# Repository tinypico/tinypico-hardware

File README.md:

# tinypico-hardware
Hardware design files for TinyPICO and Shields

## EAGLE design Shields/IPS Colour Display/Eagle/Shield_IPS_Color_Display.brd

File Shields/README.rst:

TinyPICO Hardware
=================

In this repository, you'll find Eagle 9.x design files and gerbers for the TinyPICO shields we design ourselves.

Gerber files are provided in 274X format.

As we release new shields and designed, we will add them here. 

Open Source License
-------------------

These files are released as open source under the CERN license. Please review the license before using these files in your own projects to understand your obligations.

TinyPICO Branding
-----------------
The name TinyPICO, logos and TinyPICO brand are owned by Unexpected Maker. If you would like to use the name in a project you are making that supports the TinyPICO hardware, please contact us and we'll be happy to talk to you about it.

Support Unexpected Maker
------------------------

We love designing, making and releasing our projects as open source. We do it because we believe it’s important to share knowledge and give back to the community as many have done before us. It helps us all learn and grow.

That said, a lot of time, effort and finances have gone into designing and releasing these files, so please consider supporting us by backing TinyPICO on our Crowd Supply campaign:

https://www.crowdsupply.com/unexpected-maker/tinypico

Or by buying one of our products on tindie or our own shop:

https://www.tindie.com/stores/seonr/
https://unexpectedmaker.com/shop

Or by becoming a Patron:

https://www.patreon.com/unexpectedmaker

Unexpected Maker
===================
http://youtube.com/c/unexpectedmaker

http://twitter.com/unexpectedmaker

https://www.facebook.com/unexpectedmaker/

https://www.instagram.com/unexpectedmaker/

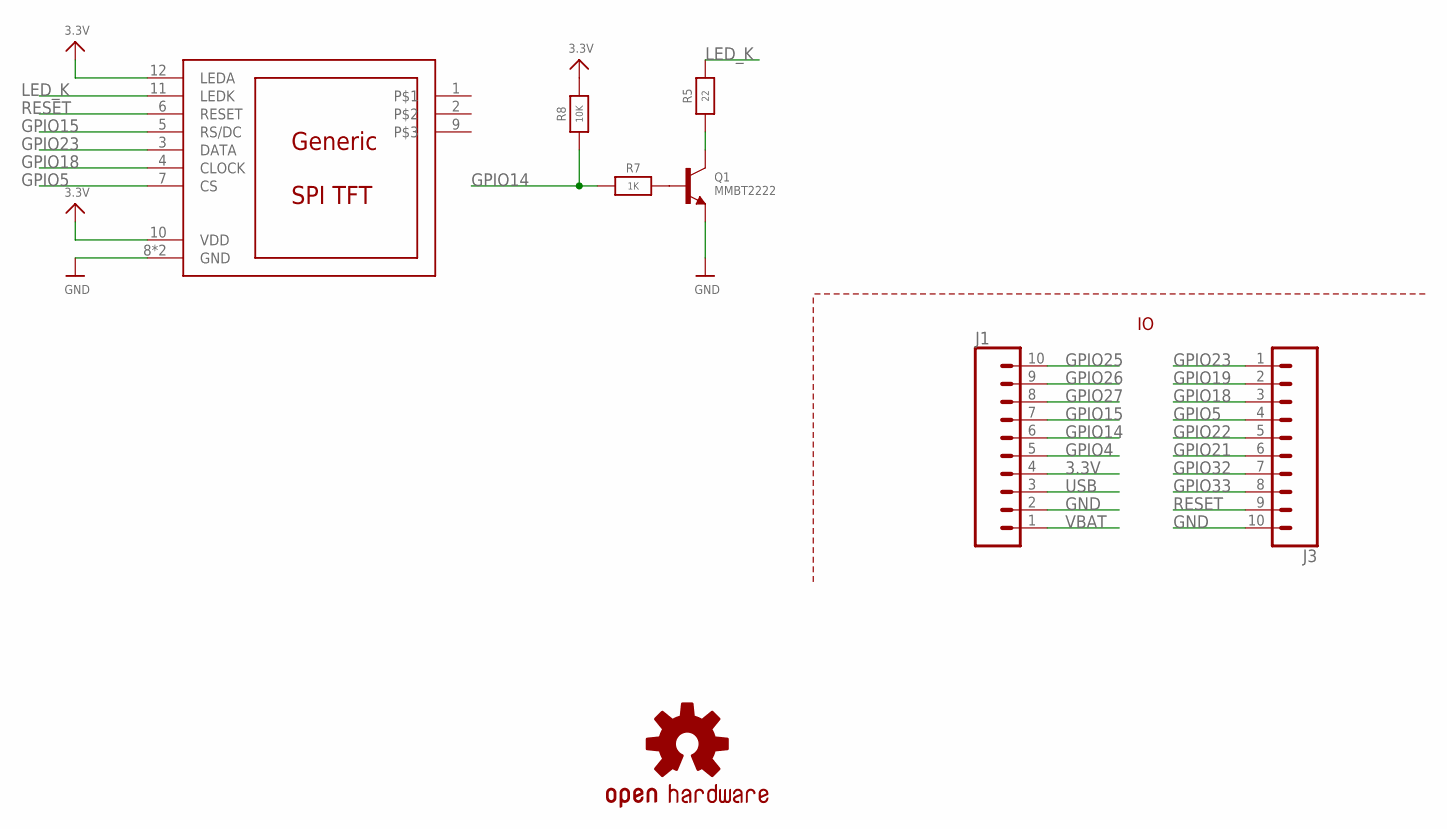
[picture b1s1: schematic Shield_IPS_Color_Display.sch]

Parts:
J1, J3: TINYPICO_HEADER_10SQR; 1X10_NO_SILK_SQR
LOGO1: OSHW-LOGOS; OSHW-LOGO-S
Q1: MMBT2222; SOT23-WIDE
R5: 22; _0603MP
R7: 1K; _0603MP
R8: 10K; _0603MP
U$2: MICROBUILDER_DISP_LCD_0.9IN_160X80; MICROBUILDER_TFT_0.96IN_160X80

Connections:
3.3V: J1.4, R8.2, U$2.10 (VDD), U$2.12 (LEDA)
GND: J1.2, J3.10, Q1.2 (E), U$2.8 (GND), U$2.13 (GND)
GPIO4: J1.5
GPIO5: J3.4, U$2.7 (CS)
GPIO14: J1.6, R7.1, R8.1
GPIO15: J1.7, U$2.5 (RS/DC)
GPIO18: J3.3, U$2.4 (CLOCK)
GPIO19: J3.2
GPIO21: J3.6
GPIO22: J3.5
GPIO23: J3.1, U$2.3 (DATA)
GPIO25: J1.10
GPIO26: J1.9
GPIO27: J1.8
GPIO32: J3.7
GPIO33: J3.8
LED_K: R5.2, U$2.11 (LEDK)
unnamed: Q1.1 (B), R7.2
unnamed: Q1.3 (C), R5.1
RESET: J3.9, U$2.6 (RESET)
USB: J1.3
VBAT: J1.1

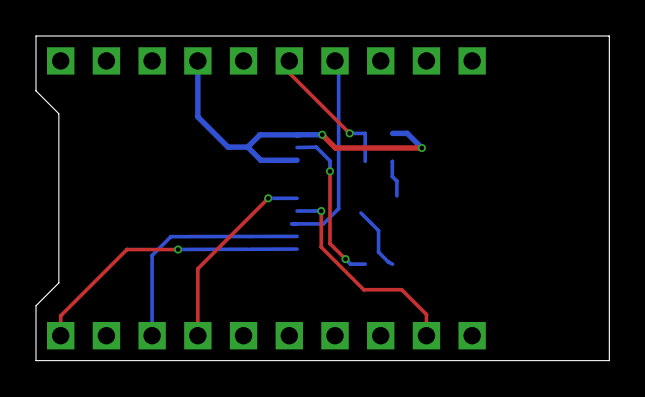
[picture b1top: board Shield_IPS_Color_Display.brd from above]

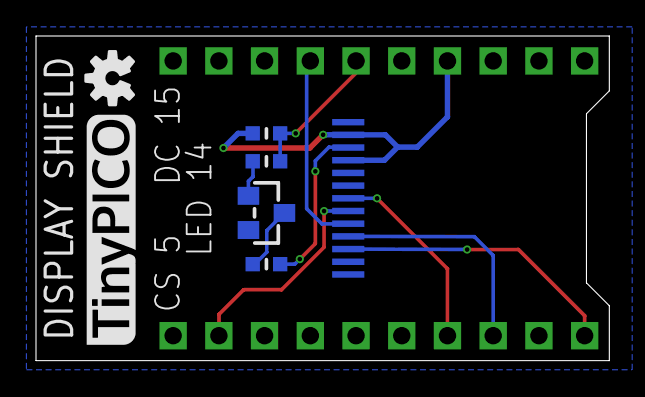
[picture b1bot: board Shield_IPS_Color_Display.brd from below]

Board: 2 copper layers, 31.9 x 18.0 mm, 8 parts (6 on the bottom side), 11 nets.

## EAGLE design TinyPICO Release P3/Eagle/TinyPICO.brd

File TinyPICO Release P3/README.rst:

TinyPICO Production Release vP3
===============================

In this repository, you'll find Eagle 9.x design files and gerbers for the production vP3 release of TinyPICO.

Open Source License
-------------------

These files are released as open source under the CERN license. Please review the license before using these files in your own projects to understand your obligations.

TinyPICO Branding
-----------------
The names TinyPICO, TinyPICO logos and TinyPICO brand are owned by Unexpected Maker. If you would like to use the name in a project you are making that supports the TinyPICO hardware, please contact us and we'll be happy to talk to you about it.

Support Unexpected Maker
------------------------

We love designing, making and releasing our projects as open source. We do it because we believe it’s important to share knowledge and give back to the community as many have done before us. It helps us all learn and grow.

That said, a lot of time, effort and finances have gone into designing and releasing these files, so please consider supporting us by backing TinyPICO on our Crowd Supply campaign:

https://www.crowdsupply.com/unexpected-maker/tinypico

Or by buying one of our products on tindie or our own shop:

https://www.tindie.com/stores/seonr/
https://unexpectedmaker.com/shop

Or by becoming a Patron:

https://www.patreon.com/unexpectedmaker

Unexpected Maker
===================
http://youtube.com/c/unexpectedmaker

http://twitter.com/unexpectedmaker

https://www.facebook.com/unexpectedmaker/

https://www.instagram.com/unexpectedmaker/

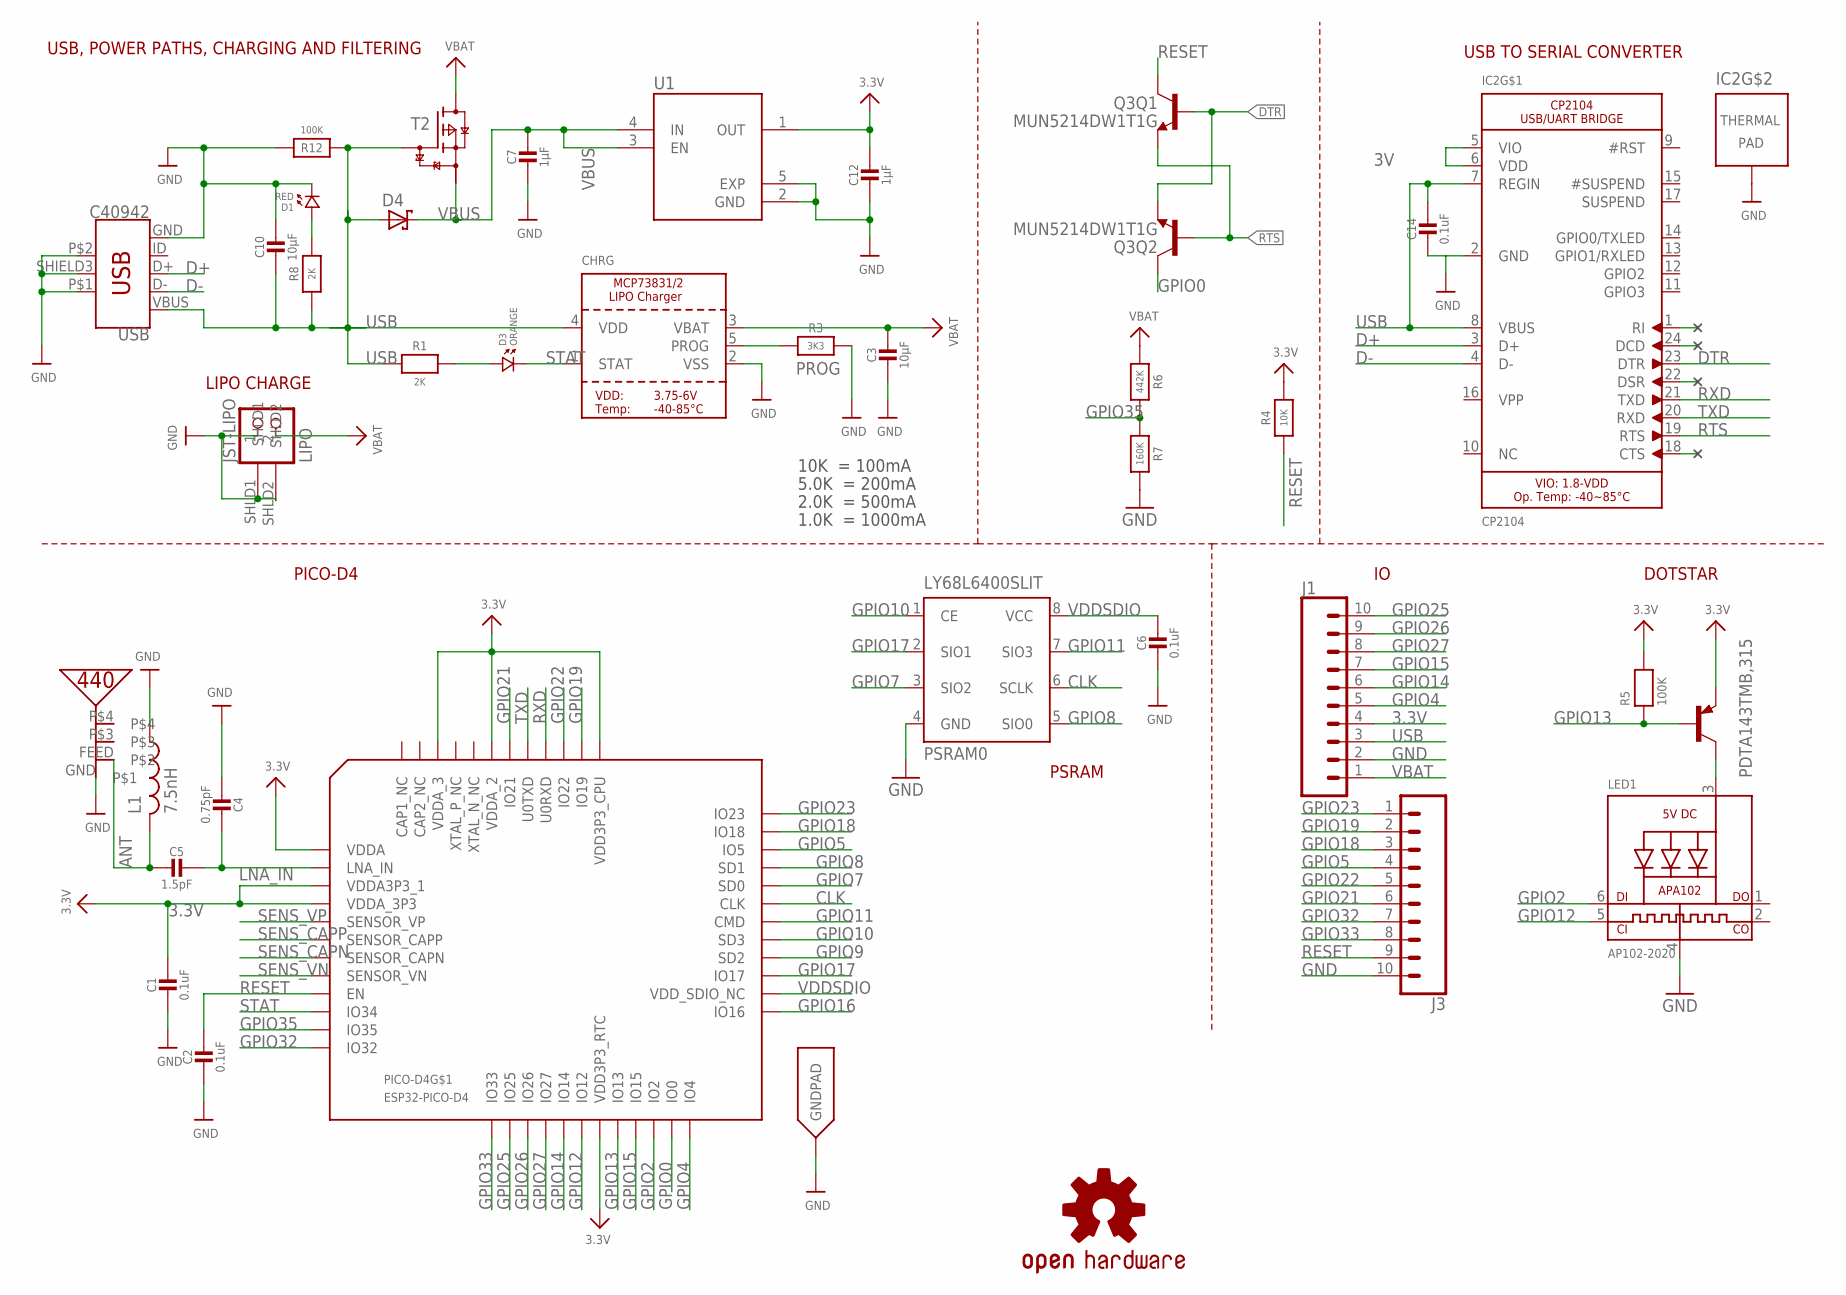
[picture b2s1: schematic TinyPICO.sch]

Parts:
C1, C2, C6, C14: 0.1uF; _0402MP
C3, C10: 10µF; _0603MP
C4: 0.75pF; _0402MP
C5: 1.5pF; _0402MP
C7, C12: 1µF; _0402MP
CHRG: TP4065-4.2V-SOT25-R; SOT23-5
D1: RED; 0402.LED
D3: ORANGE; 0402.LED
D4: BAT60J; SOD323_ST
IC2: CP2104; MICROBUILDER_QFN24_4MM_SMSC
J1, J3: TINYPICO_HEADER_10NO_SILK_PTH_FEMALE; 1X10_NO_SILK
JST-LIPO: LIPO; JSTPH2
L1: 7.5nH; RESC0402_N
LED1: AP102-2020; MICROBUILDER_APA102_2020
LOGO1: OSHW-LOGOS; OSHW-LOGO-S
LY68L6400SLIT: PSRAM0; SOP8
PDTA143TMB,315: TINYPICO-PNPAMB; SOT883(B)
PICO-D4: ESP32-PICO-D4; PICO-D4-QFN48
Q3: MUN5214DW1T1G; DUAL_NPN_SC70-6
R1, R8: 2K; _0402MP
R3: 3K3; _0402MP
R4: 10K; _0402MP
R5, R12: 100K; _0402MP
R6: 442K; _0402MP
R7: 160K; _0402MP
T2: TINYPICO-P-FETKMB; SOT883(B)
U1: NCP170AMX300TCG; VREG_NCP170AMX300TCG
U$8: PRO-OB-440
USB: C40942; USB-B-MICRO-SMD

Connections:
3.3V: C1.1, C12.1, J1.4, PDTA143TMB,315.2 (E), PICO-D4.1 (VDDA), PICO-D4.3 (VDDA3P3_1), PICO-D4.4 (VDDA_3P3), PICO-D4.19 (VDD3P3_RTC), PICO-D4.37 (VDD3P3_CPU), PICO-D4.43 (VDDA_2), PICO-D4.46 (VDDA_3), R4.2, R5.2, U1.1 (OUT)
3V: IC2.5 (VIO), IC2.6 (VDD)
ANT: C5.2, L1.2, U$8.FEED
CLK: LY68L6400SLIT.6 (SCLK), PICO-D4.31 (CLK)
D+: IC2.3 (D+), USB.D+
D-: IC2.4 (D-), USB.D-
DTR: IC2.23 (DTR), Q3.1 (E), Q3.5 (B)
GND: C1.2, C2.2, C3.2, C4.2, C6.2, C7.2, C10.1, C12.2, C14.2, CHRG.2 (VSS), D1.P$2 (2), IC2.2 (GND), IC2.THERM (TP), J1.2, J3.10, JST-LIPO.1, JST-LIPO.SHLD1, JST-LIPO.SHLD2, L1.1, LED1.4 (GND), LY68L6400SLIT.4 (GND), PICO-D4.EXP (GNDPAD), R3.2, R7.2, R12.2, U1.2 (GND), U1.5 (EXP), U$8.GND, USB.GND, USB.P$1 (SHIELD1), USB.P$2 (SHIELD2), USB.SHIELD3 (SHIELD)
GPIO0: PICO-D4.23 (IO0), Q3.6 (C)
GPIO2: LED1.6 (DI), PICO-D4.22 (IO2)
GPIO4: J1.5, PICO-D4.24 (IO4)
GPIO5: J3.4, PICO-D4.34 (IO5)
GPIO7: LY68L6400SLIT.3 (SIO2), PICO-D4.32 (SD0)
GPIO8: LY68L6400SLIT.5 (SIO0), PICO-D4.33 (SD1)
GPIO9: PICO-D4.28 (SD2)
GPIO10: LY68L6400SLIT.1 (CE), PICO-D4.29 (SD3)
GPIO11: LY68L6400SLIT.7 (SIO3), PICO-D4.30 (CMD)
GPIO12: LED1.5 (CKI), PICO-D4.18 (IO12)
GPIO13: PDTA143TMB,315.1 (B), PICO-D4.20 (IO13), R5.1
GPIO14: J1.6, PICO-D4.17 (IO14)
GPIO15: J1.7, PICO-D4.21 (IO15)
GPIO16: PICO-D4.25 (IO16)
GPIO17: LY68L6400SLIT.2 (SIO1), PICO-D4.27 (IO17)
GPIO18: J3.3, PICO-D4.35 (IO18)
GPIO19: J3.2, PICO-D4.38 (IO19)
GPIO21: J3.6, PICO-D4.42 (IO21)
GPIO22: J3.5, PICO-D4.39 (IO22)
GPIO23: J3.1, PICO-D4.36 (IO23)
GPIO25: J1.10, PICO-D4.14 (IO25)
GPIO26: J1.9, PICO-D4.15 (IO26)
GPIO27: J1.8, PICO-D4.16 (IO27)
GPIO32: J3.7, PICO-D4.12 (IO32)
GPIO33: J3.8, PICO-D4.13 (IO33)
GPIO35: PICO-D4.11 (IO35), R6.2, R7.1
LNA_IN: C4.1, C5.1, PICO-D4.2 (LNA_IN)
unnamed: D1.P$1 (1), R8.2
unnamed: D3.P$1 (1), R1.2
unnamed: LED1.3 (VDD), PDTA143TMB,315.3 (C)
PROG: CHRG.5 (PROG), R3.1
RESET: C2.1, J3.9, PICO-D4.9 (EN), Q3.3 (C), R4.1
RTS: IC2.19 (RTS), Q3.2 (B), Q3.4 (E)
RXD: IC2.21 (TXD), PICO-D4.40 (U0RXD)
SENS_CAPN: PICO-D4.7 (SENSOR_CAPN)
SENS_CAPP: PICO-D4.6 (SENSOR_CAPP)
SENS_VN: PICO-D4.8 (SENSOR_VN)
SENS_VP: PICO-D4.5 (SENSOR_VP)
STAT: CHRG.1 (STAT), D3.P$2 (2), PICO-D4.10 (IO34)
TXD: IC2.20 (RXD), PICO-D4.41 (U0TXD)
USB: C10.2, C14.1, CHRG.4 (VDD), D4.A, IC2.7 (REGIN), IC2.8 (VBUS), J1.3, R1.1, R8.1, R12.1, T2.1 (G), USB.VBUS
VBAT: C3.1, CHRG.3 (VBAT), J1.1, JST-LIPO.2, R6.1, T2.3 (D)
VBUS: C7.1, D4.C, T2.2 (S), U1.3 (EN), U1.4 (IN)
VDDSDIO: C6.1, LY68L6400SLIT.8 (VCC), PICO-D4.26 (VDD_SDIO_NC)

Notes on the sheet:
USB, POWER PATHS, CHARGING AND FILTERING
LIPO CHARGE
USB TO SERIAL CONVERTER
PICO-D4
10K = 100mA
5.0K = 200mA
2.0K = 500mA
1.0K = 1000mA
PSRAM
DOTSTAR

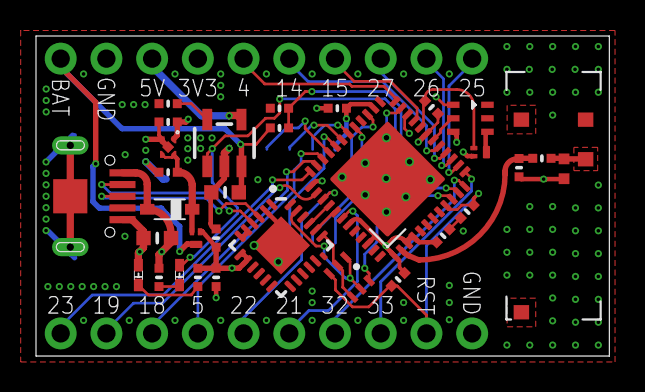
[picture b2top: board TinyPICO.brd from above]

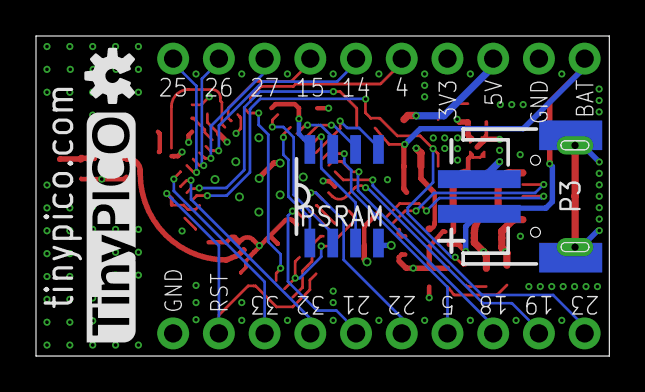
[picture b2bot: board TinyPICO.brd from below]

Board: 4 copper layers, 31.9 x 17.8 mm, 37 parts (3 on the bottom side), 46 nets.

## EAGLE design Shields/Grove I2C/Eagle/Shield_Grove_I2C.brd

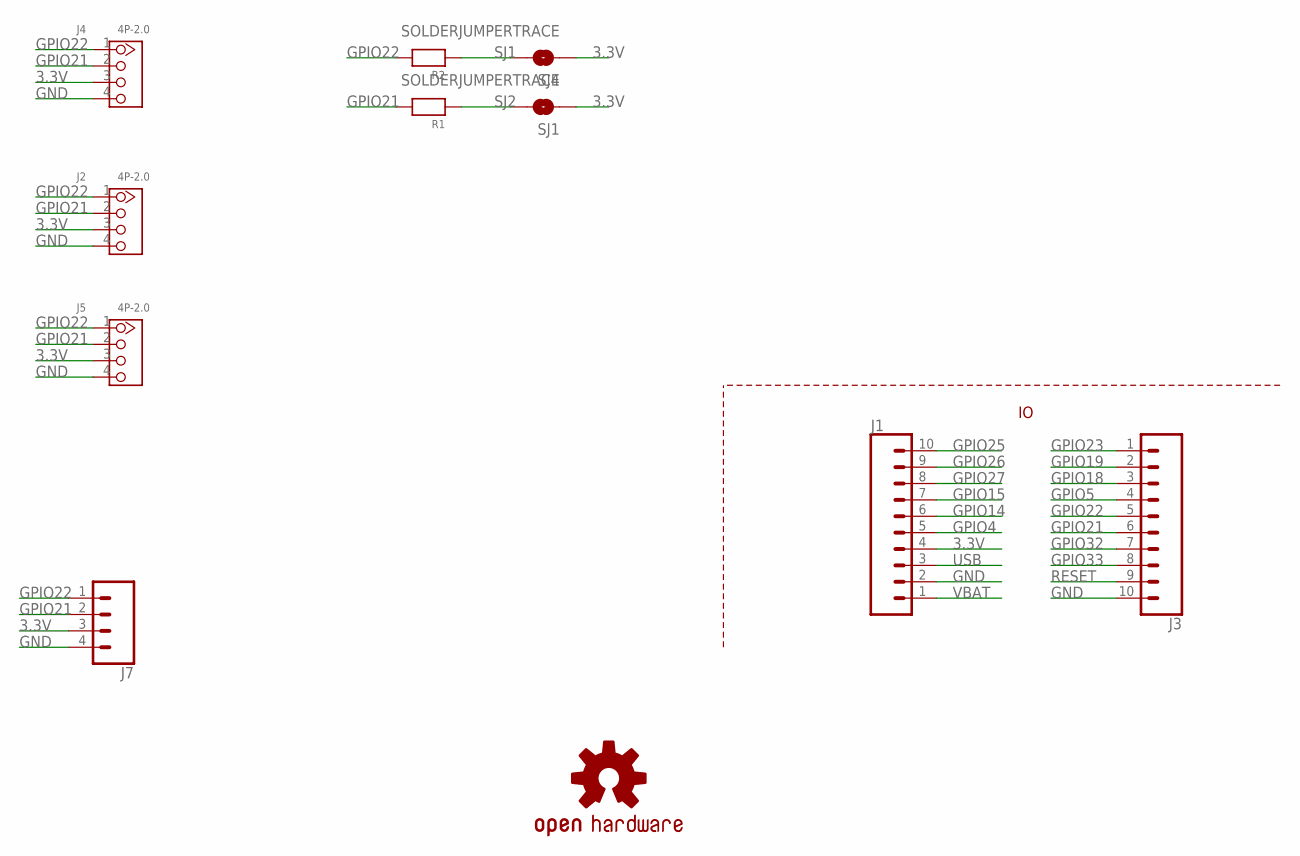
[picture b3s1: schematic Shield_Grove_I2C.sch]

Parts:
J1, J3: TINYPICO_HEADER_10NO_SILK_PTH_FEMALE; 1X10_NO_SILK
J2, J4, J5: 4P-2.0; HW4-2.0
J7: CONN_041X04_NO_SILK; 1X04_NO_SILK
LOGO1: OSHW-LOGOS; OSHW-LOGO-S
R1, R2: RESISTOR_0603MP; _0603MP
SJ1, SJ4: SOLDERJUMPERTRACE; SPARKFUN_SJ_2S-TRACE

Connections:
3.3V: J1.4, J2.3, J4.3, J5.3, J7.3, SJ1.1, SJ4.1
GND: J1.2, J2.4, J3.10, J4.4, J5.4, J7.4
GPIO4: J1.5
GPIO5: J3.4
GPIO14: J1.6
GPIO15: J1.7
GPIO18: J3.3
GPIO19: J3.2
GPIO21: J2.2, J3.6, J4.2, J5.2, J7.2, R1.2
GPIO22: J2.1, J3.5, J4.1, J5.1, J7.1, R2.2
GPIO23: J3.1
GPIO25: J1.10
GPIO26: J1.9
GPIO27: J1.8
GPIO32: J3.7
GPIO33: J3.8
RESET: J3.9
SJ1: R2.1, SJ4.2
SJ2: R1.1, SJ1.2
USB: J1.3
VBAT: J1.1

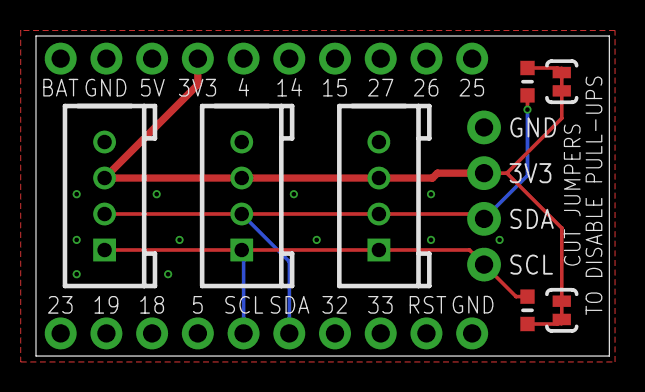
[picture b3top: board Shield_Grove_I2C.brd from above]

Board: 2 copper layers, 31.9 x 17.8 mm, 11 parts (1 on the bottom side), 6 nets.

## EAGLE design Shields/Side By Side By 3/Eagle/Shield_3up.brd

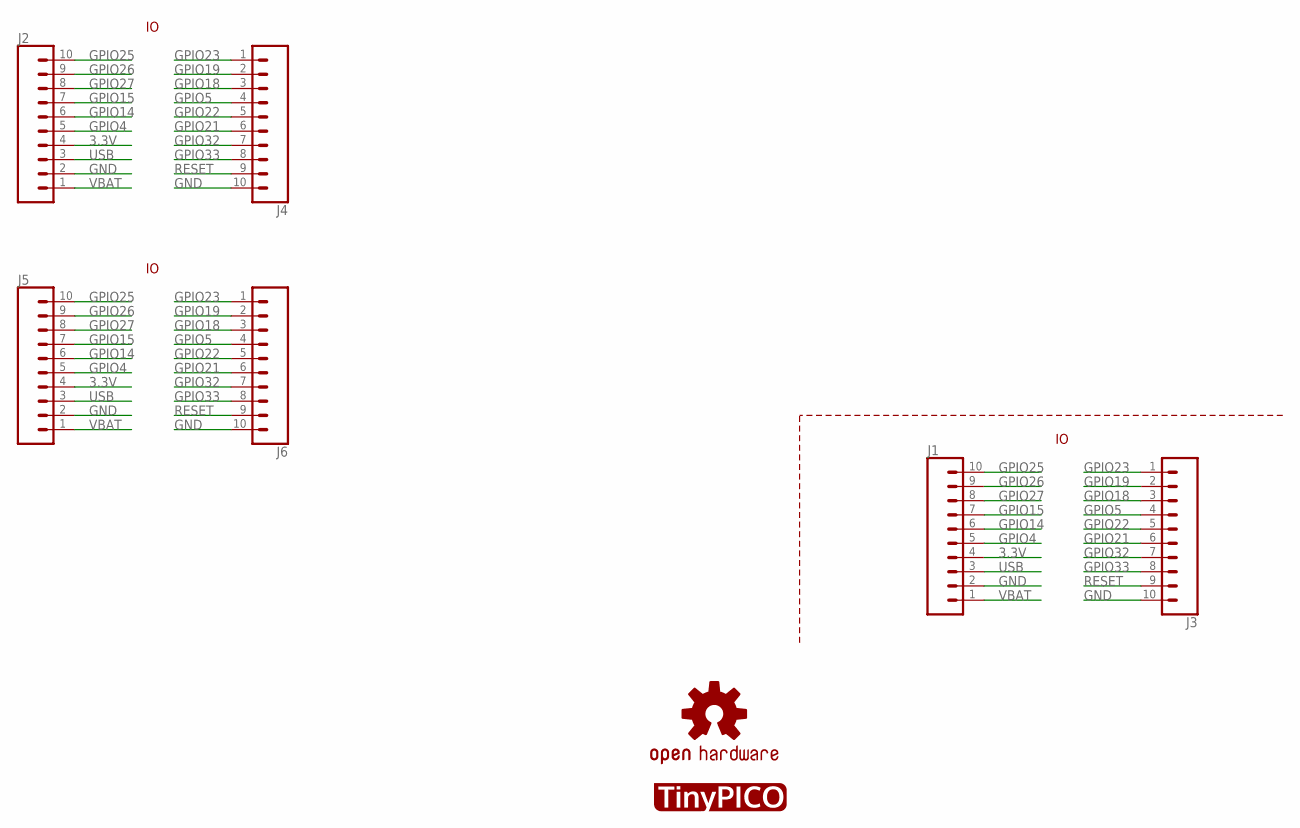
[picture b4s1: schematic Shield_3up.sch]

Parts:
J1, J2, J3, J4, J5, J6: TINYPICO_HEADER_10NO_SILK_PTH_FEMALE; 1X10_NO_SILK
LOGO1: OSHW-LOGOS; OSHW-LOGO-S
U$1: TP_LOGO

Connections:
3.3V: J1.4, J2.4, J5.4
GND: J1.2, J2.2, J3.10, J4.10, J5.2, J6.10
GPIO4: J1.5, J2.5, J5.5
GPIO5: J3.4, J4.4, J6.4
GPIO14: J1.6, J2.6, J5.6
GPIO15: J1.7, J2.7, J5.7
GPIO18: J3.3, J4.3, J6.3
GPIO19: J3.2, J4.2, J6.2
GPIO21: J3.6, J4.6, J6.6
GPIO22: J3.5, J4.5, J6.5
GPIO23: J3.1, J4.1, J6.1
GPIO25: J1.10, J2.10, J5.10
GPIO26: J1.9, J2.9, J5.9
GPIO27: J1.8, J2.8, J5.8
GPIO32: J3.7, J4.7, J6.7
GPIO33: J3.8, J4.8, J6.8
RESET: J3.9, J4.9, J6.9
USB: J1.3, J2.3, J5.3
VBAT: J1.1, J2.1, J5.1

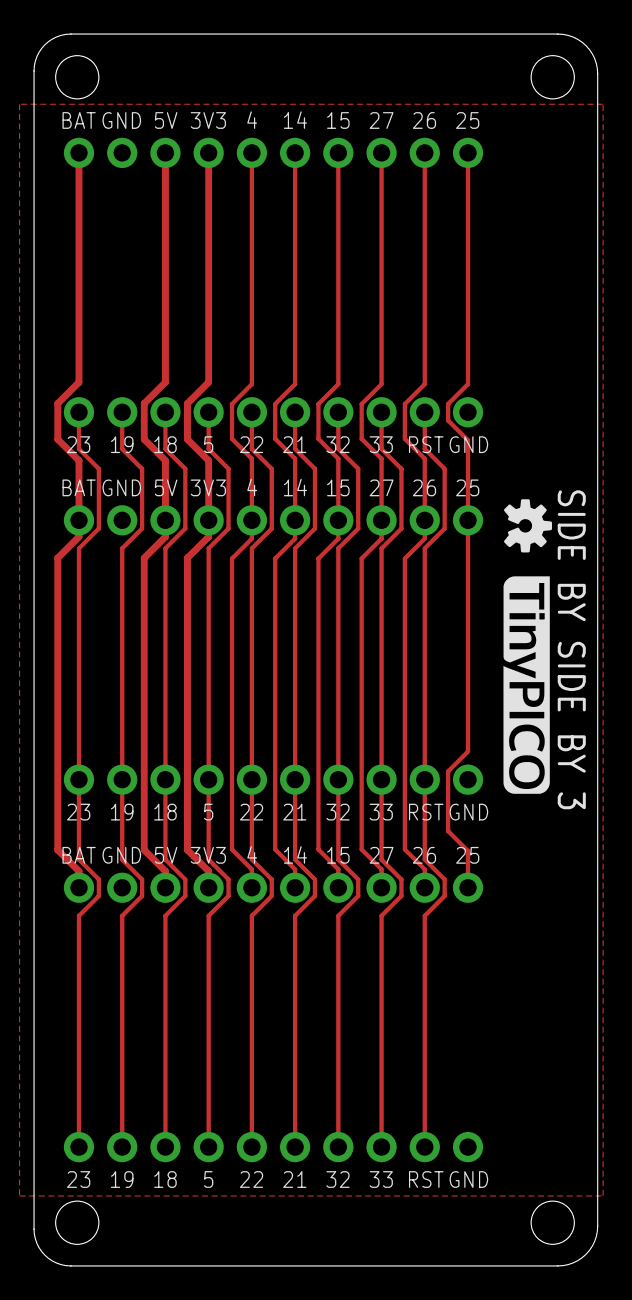
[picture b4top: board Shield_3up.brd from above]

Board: 2 copper layers, 33.1 x 72.4 mm, 8 parts (1 on the bottom side), 19 nets.

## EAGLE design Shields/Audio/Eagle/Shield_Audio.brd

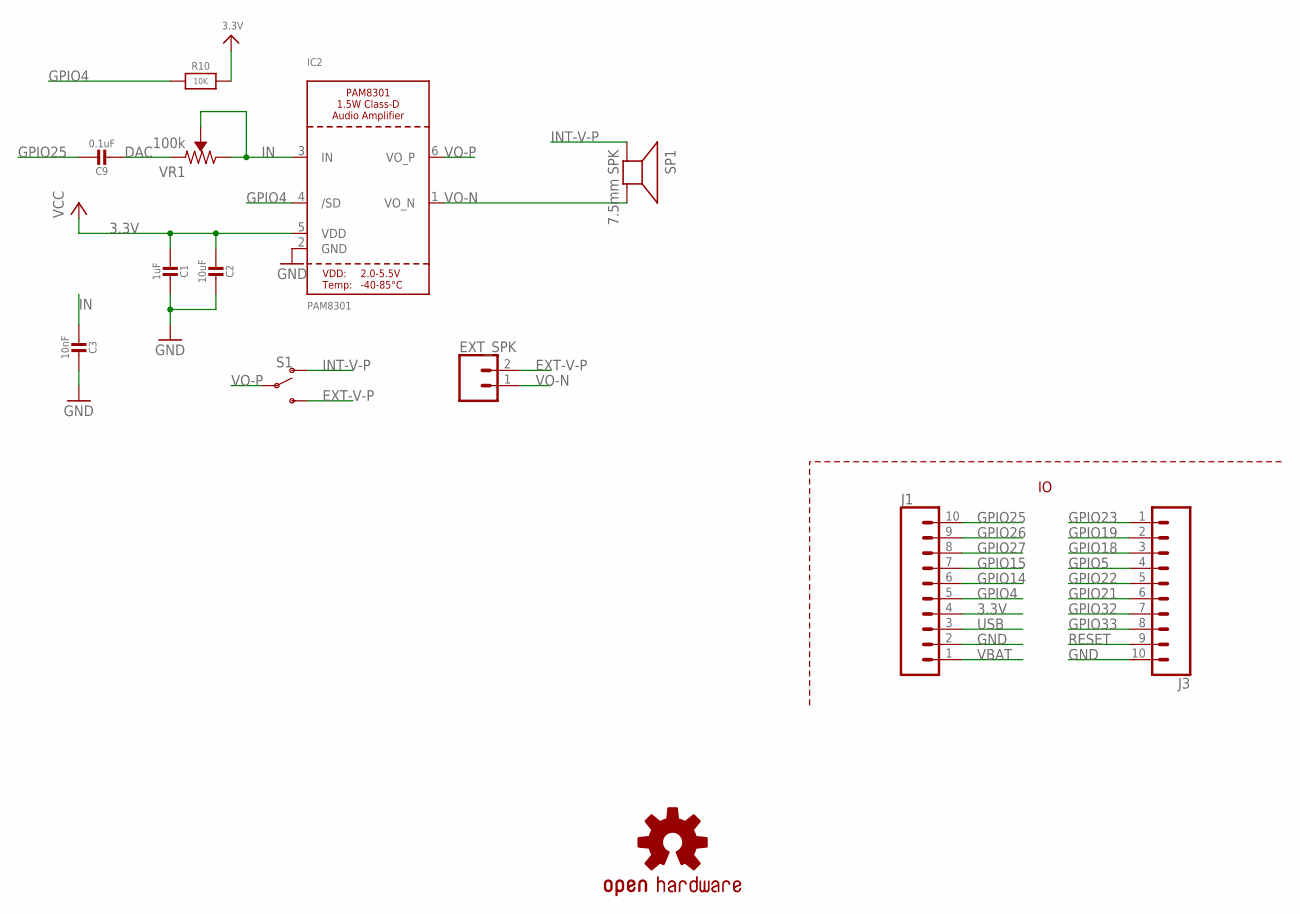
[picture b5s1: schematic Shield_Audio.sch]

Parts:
C1: 1uF; _0603MP
C2: 10uF; _0603MP
C3: 10nF; _0603MP
C9: 0.1uF; _0603MP
EXT_SPK: CONN_021X02_NO_SILK; 1X02_NO_SILK
IC2: PAM8301; SOT23-6
J1, J3: TINYPICO_HEADER_10NO_SILK_PTH_FEMALE; 1X10_NO_SILK
LOGO1: OSHW-LOGOS; OSHW-LOGO-S
R10: 10K; _0603MP
S1: SPARKFUN-SWITCHES_SWITCH-SPDT-SMD-RIGHT-ANGLE; SPARKFUN-SWITCHES_SWITCH_SPST_SMD_A
SP1: 7.5mm SPK; BUZZER_SMT_7.5MM
VR1: 100k; TRIMPOT-SMD-5MM

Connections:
3.3V: C1.2, C2.2, IC2.5 (VDD), J1.4, R10.2
DAC: C9.2, VR1.A (CCW)
EXT-V-P: EXT_SPK.2, S1.3 (S)
GND: C1.1, C2.1, C3.1, IC2.2 (GND), J1.2, J3.10
GPIO4: IC2.4 (/SD), J1.5, R10.1
GPIO5: J3.4
GPIO14: J1.6
GPIO15: J1.7
GPIO18: J3.3
GPIO19: J3.2
GPIO21: J3.6
GPIO22: J3.5
GPIO23: J3.1
GPIO25: C9.1, J1.10
GPIO26: J1.9
GPIO27: J1.8
GPIO32: J3.7
GPIO33: J3.8
IN: C3.2, IC2.3 (IN), VR1.B (WIPER), VR1.C (CW)
INT-V-P: S1.1 (O), SP1.+
RESET: J3.9
USB: J1.3
VBAT: J1.1
VO-N: EXT_SPK.1, IC2.1 (VO_N), SP1.-
VO-P: IC2.6 (VO_P), S1.2

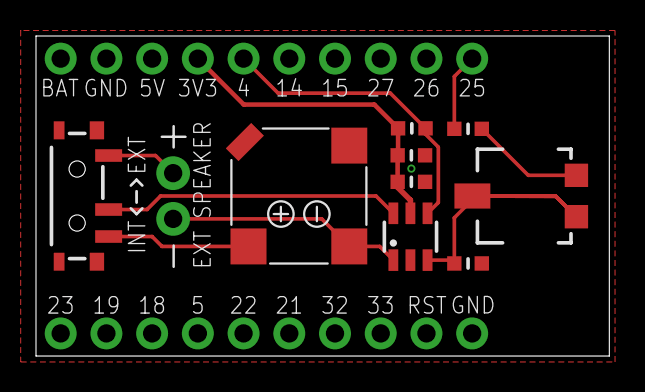
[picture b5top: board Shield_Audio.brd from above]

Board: 2 copper layers, 31.9 x 17.8 mm, 13 parts (1 on the bottom side), 10 nets.

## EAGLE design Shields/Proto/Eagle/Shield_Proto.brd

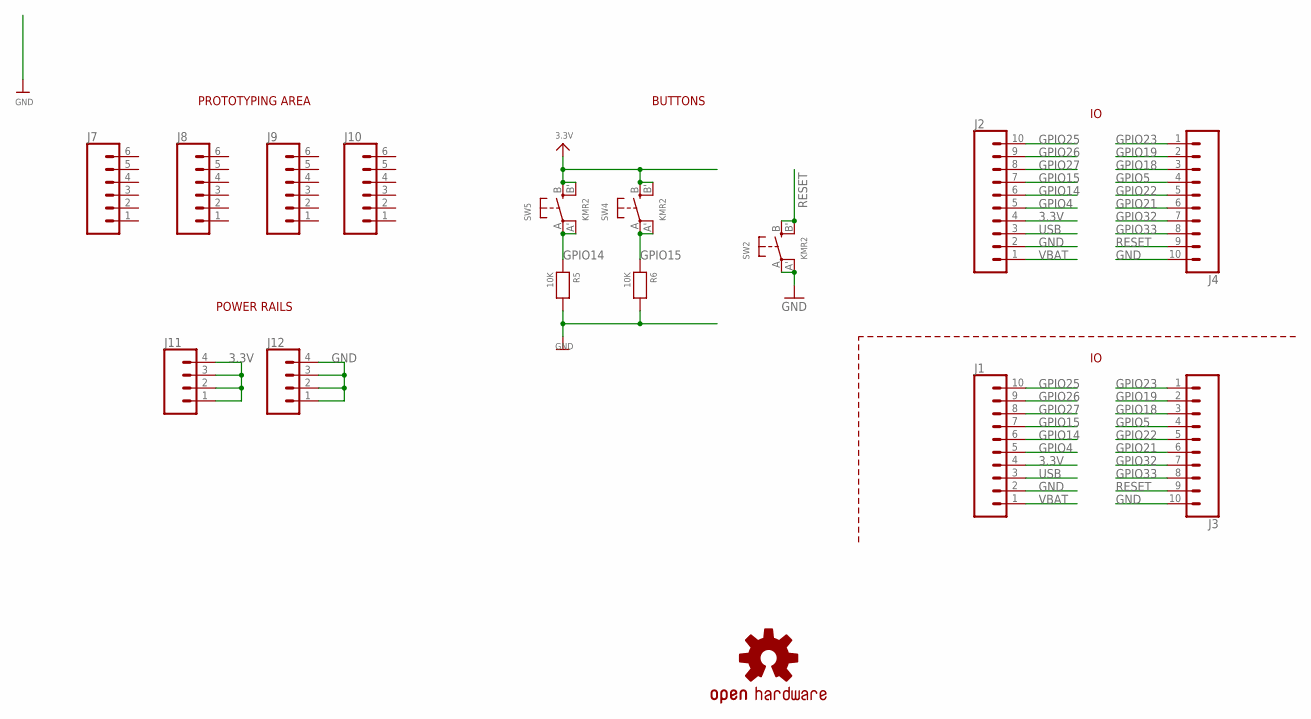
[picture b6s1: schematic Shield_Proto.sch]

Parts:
J1, J2, J3, J4: TINYPICO_HEADER_10NO_SILK_PTH_FEMALE; 1X10_NO_SILK
J7, J8, J9, J10: CONNECTORS_CONN_06NO_SILK_NO_POP; SPARKFUN-CONNECTORS_1X06_NO_SILK
J11, J12: CONN_041X04_NO_SILK; 1X04_NO_SILK
LOGO1: OSHW-LOGOS; OSHW-LOGO-S
R5, R6: 10K; _0603MP
SW2, SW4, SW5: KMR2; BTN_KMR2_4.6X2.8

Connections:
3.3V: J1.4, J2.4, J11.1, J11.2, J11.3, J11.4, SW4.B (S), SW4.B' (S1), SW5.B (S), SW5.B' (S1)
GND: J1.2, J2.2, J3.10, J4.10, J12.1, J12.2, J12.3, J12.4, R5.2, R6.2, SW2.A, SW2.A' (P1)
GPIO4: J1.5, J2.5
GPIO5: J3.4, J4.4
GPIO14: J1.6, J2.6, R5.1, SW5.A, SW5.A' (P1)
GPIO15: J1.7, J2.7, R6.1, SW4.A, SW4.A' (P1)
GPIO18: J3.3, J4.3
GPIO19: J3.2, J4.2
GPIO21: J3.6, J4.6
GPIO22: J3.5, J4.5
GPIO23: J3.1, J4.1
GPIO25: J1.10, J2.10
GPIO26: J1.9, J2.9
GPIO27: J1.8, J2.8
GPIO32: J3.7, J4.7
GPIO33: J3.8, J4.8
RESET: J3.9, J4.9, SW2.B (S), SW2.B' (S1)
USB: J1.3, J2.3
VBAT: J1.1, J2.1

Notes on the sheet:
PROTOTYPING AREA
POWER RAILS
BUTTONS

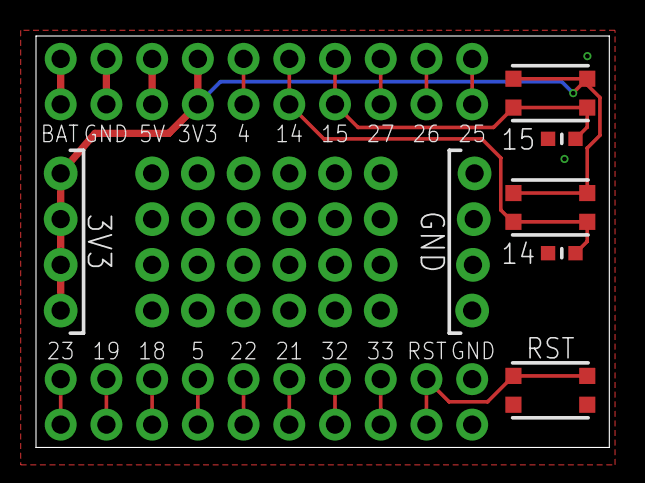
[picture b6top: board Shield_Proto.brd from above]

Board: 2 copper layers, 31.9 x 22.9 mm, 16 parts (1 on the bottom side), 19 nets.

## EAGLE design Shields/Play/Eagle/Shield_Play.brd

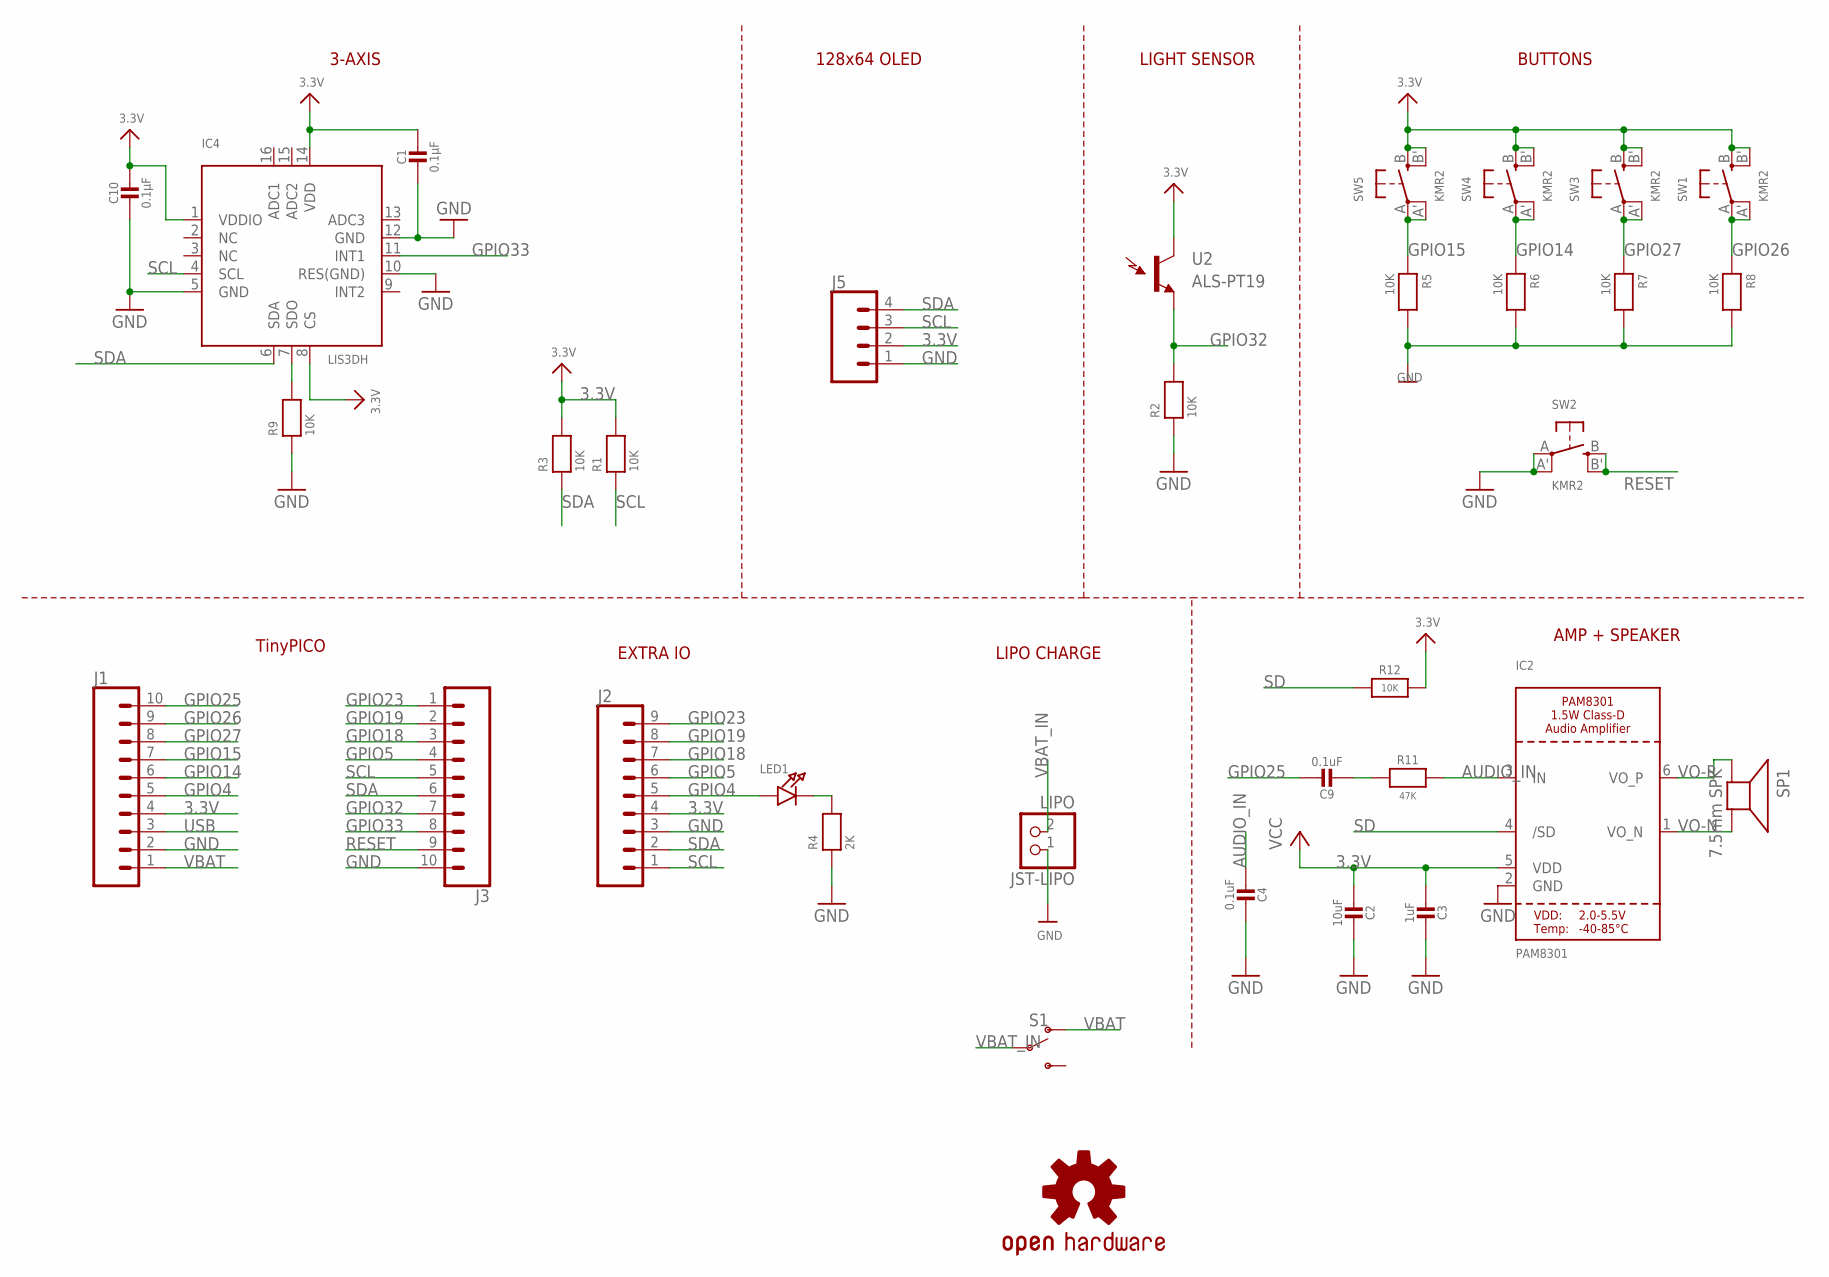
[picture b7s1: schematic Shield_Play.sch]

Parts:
C1, C10: 0.1µF; _0603MP
C2: 10uF; _0603MP
C3: 1uF; _0603MP
C4, C9: 0.1uF; _0603MP
IC2: PAM8301; SOT23-6
IC4: LIS3DH; LGA16_3X3MM
J1, J3: TINYPICO_HEADER_10NO_SILK_PTH_FEMALE; 1X10_NO_SILK
J2: CONN_09NO_SILK; 1X09_NO_SILK
J5: CONN_041X04_NO_SILK; 1X04_NO_SILK
JST-LIPO: LIPO; JSTPH2
LED1: LED0603_NOOUTLINE; CHIPLED_0603_NOOUTLINE
LOGO1: OSHW-LOGOS; OSHW-LOGO-S
R1, R2, R3, R5, R6, R7, R8, R9, R12: 10K; _0603MP
R4: 2K; _0603MP
R11: 47K; _0603MP
S1: SPARKFUN-SWITCHES_SWITCH-SPDT-SMD-RIGHT-ANGLE; SPARKFUN-SWITCHES_SWITCH_SPST_SMD_A
SP1: 7.5mm SPK; BUZZER_SMT_7.5MM
SW1, SW2, SW3, SW4, SW5: KMR2; BTN_KMR2_4.6X2.8
U2: ALS-PT19

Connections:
3.3V: C1.1, C2.2, C3.2, C10.1, IC2.5 (VDD), IC4.1 (VDDIO), IC4.8 (CS), IC4.14 (VDD), J1.4, J2.4, J5.2, R1.2, R3.2, R12.2, SW1.B (S), SW1.B' (S1), SW3.B (S), SW3.B' (S1), SW4.B (S), SW4.B' (S1), SW5.B (S), SW5.B' (S1), U2.C (C1)
AUDIO_IN: C4.2, IC2.3 (IN), R11.2
GND: C1.2, C2.1, C3.1, C4.1, C10.2, IC2.2 (GND), IC4.5 (GND), IC4.10 (RES(GND)), IC4.12 (GND), J1.2, J2.3, J3.10, J5.1, JST-LIPO.1, R2.1, R4.1, R5.2, R6.2, R7.2, R8.2, R9.1, SW2.A, SW2.A' (P1)
GPIO4: J1.5, J2.5, LED1.A
GPIO5: J2.6, J3.4
GPIO14: J1.6, R6.1, SW4.A, SW4.A' (P1)
GPIO15: J1.7, R5.1, SW5.A, SW5.A' (P1)
GPIO18: J2.7, J3.3
GPIO19: J2.8, J3.2
GPIO23: J2.9, J3.1
GPIO25: C9.1, J1.10
GPIO26: J1.9, R8.1, SW1.A, SW1.A' (P1)
GPIO27: J1.8, R7.1, SW3.A, SW3.A' (P1)
GPIO32: J3.7, R2.2, U2.E (E1)
GPIO33: IC4.11 (INT1), J3.8
unnamed: IC4.7 (SDO), R9.2
unnamed: LED1.C, R4.2
unnamed: C9.2, R11.1
RESET: J3.9, SW2.B (S), SW2.B' (S1)
SCL: IC4.4 (SCL), J2.1, J3.5, J5.3, R1.1
SD: IC2.4 (/SD), R12.1
SDA: IC4.6 (SDA), J2.2, J3.6, J5.4, R3.1
USB: J1.3
VBAT: J1.1, S1.1 (O)
VBAT_IN: JST-LIPO.2, S1.2
VO-N: IC2.1 (VO_N), SP1.-
VO-P: IC2.6 (VO_P), SP1.+

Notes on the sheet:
TinyPICO
LIPO CHARGE
BUTTONS
LIGHT SENSOR
3-AXIS
128x64 OLED
EXTRA IO
AMP + SPEAKER

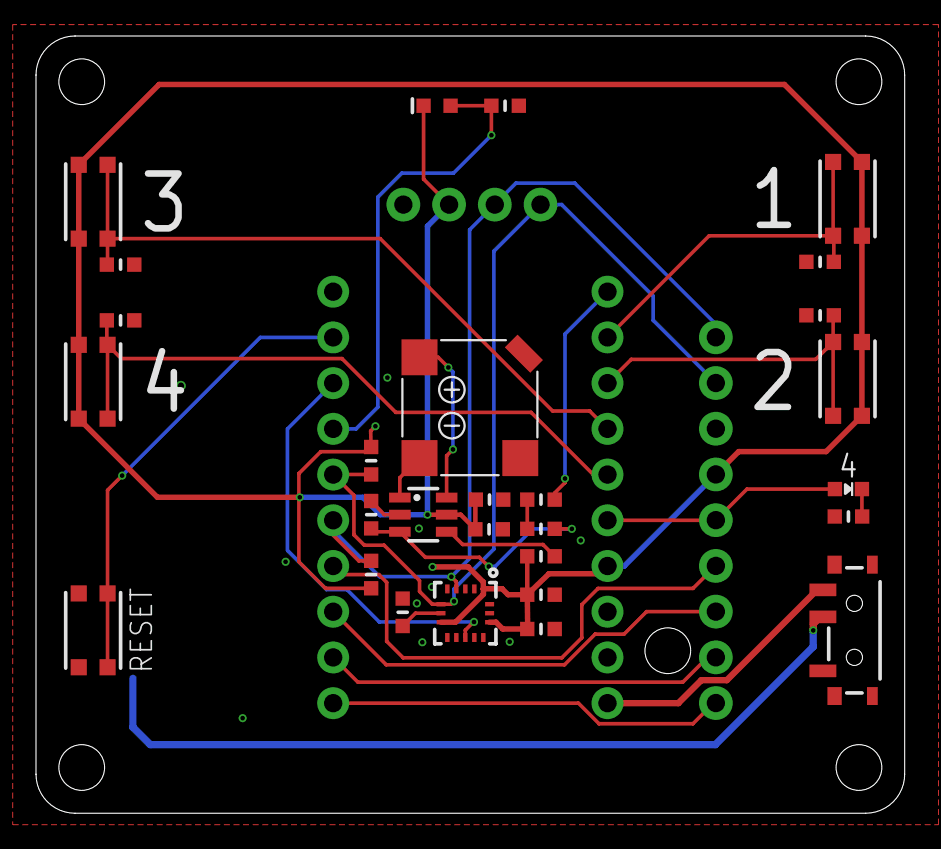
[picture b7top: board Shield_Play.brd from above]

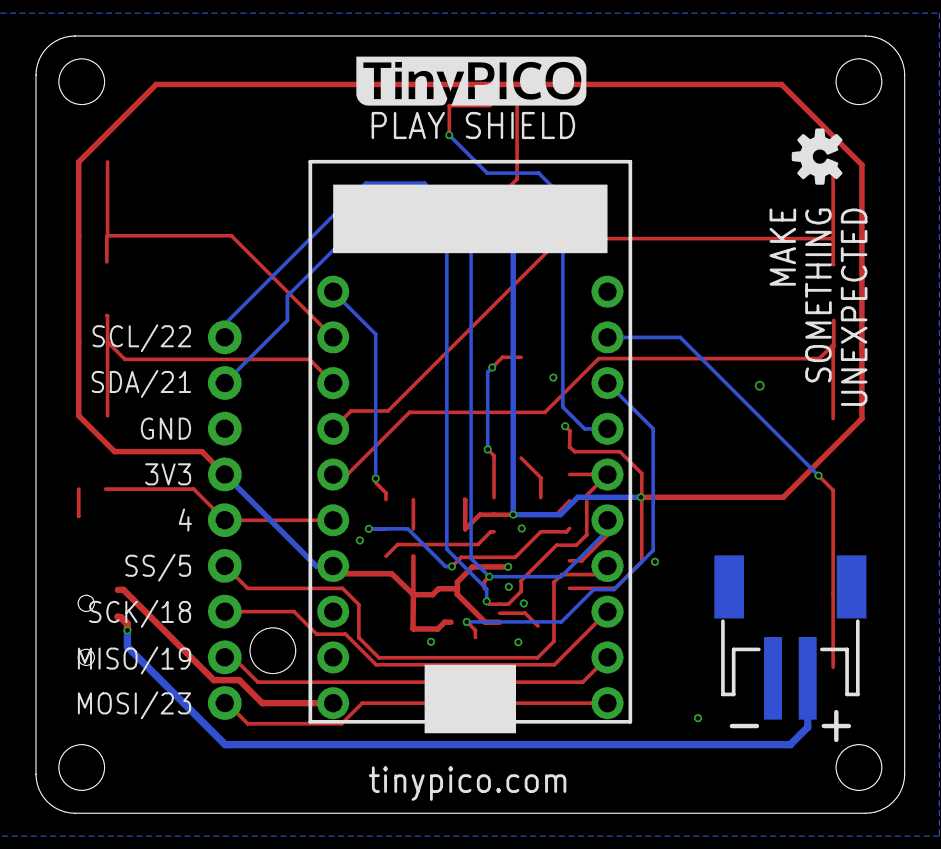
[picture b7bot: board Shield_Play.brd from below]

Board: 2 copper layers, 48.3 x 43.2 mm, 34 parts (2 on the bottom side), 26 nets.

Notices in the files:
parts and their libraries:
SparkFun-Aesthetics: Licensing: Creative Commons ShareAlike 4.0 International - https://creativecommons.org/licenses/by-sa/4.0
microbuilder: This work is placed in the public domain, and may be freely used for commercial and non-commercial work with the following conditions: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
